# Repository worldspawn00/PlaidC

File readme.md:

# Plaid type C

Redesign of the Plaid PCB to use USBC and 2u stabilized layouts

Assembly and BOM generally follows the standard Plaid with the exception of the USBC port (USB4085-GF-A GCT) and 2 additional 5.1k resistors for C to C identification.  The PCB can also now take PCB-mount 2u stabilizers for the 2u spacebar locations, clip in or screw in will work.

https://github.com/hsgw/plaid/blob/master/doc/en/soldering.md

* Keyboard Maintainer: [Worldspawn00](https://github.com/Worldspawn00)

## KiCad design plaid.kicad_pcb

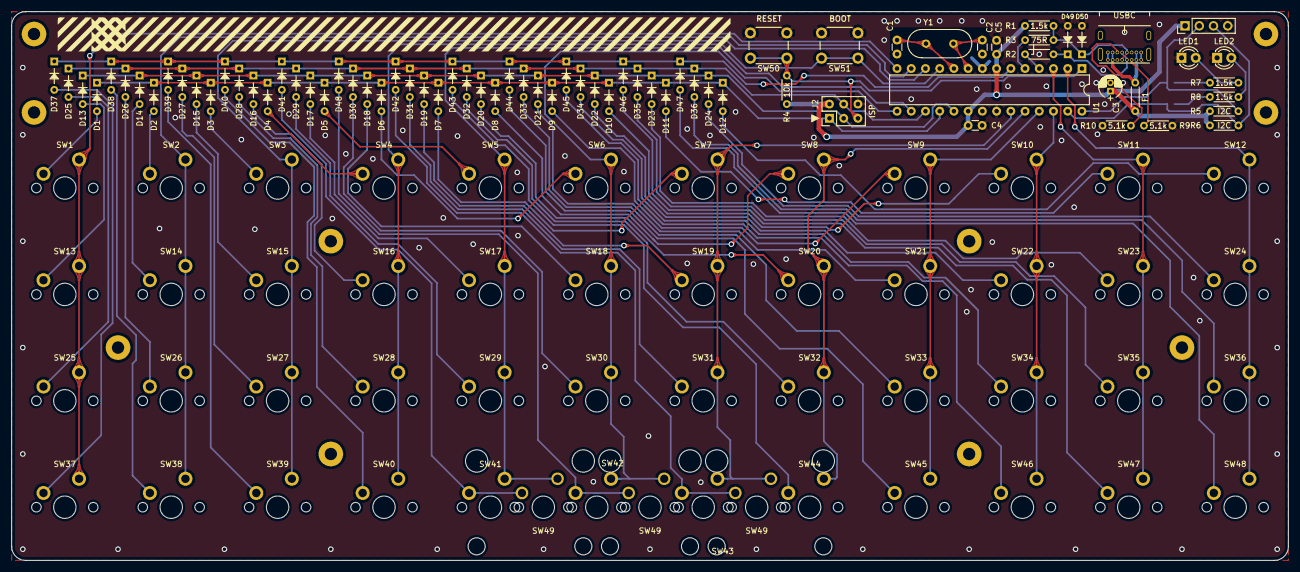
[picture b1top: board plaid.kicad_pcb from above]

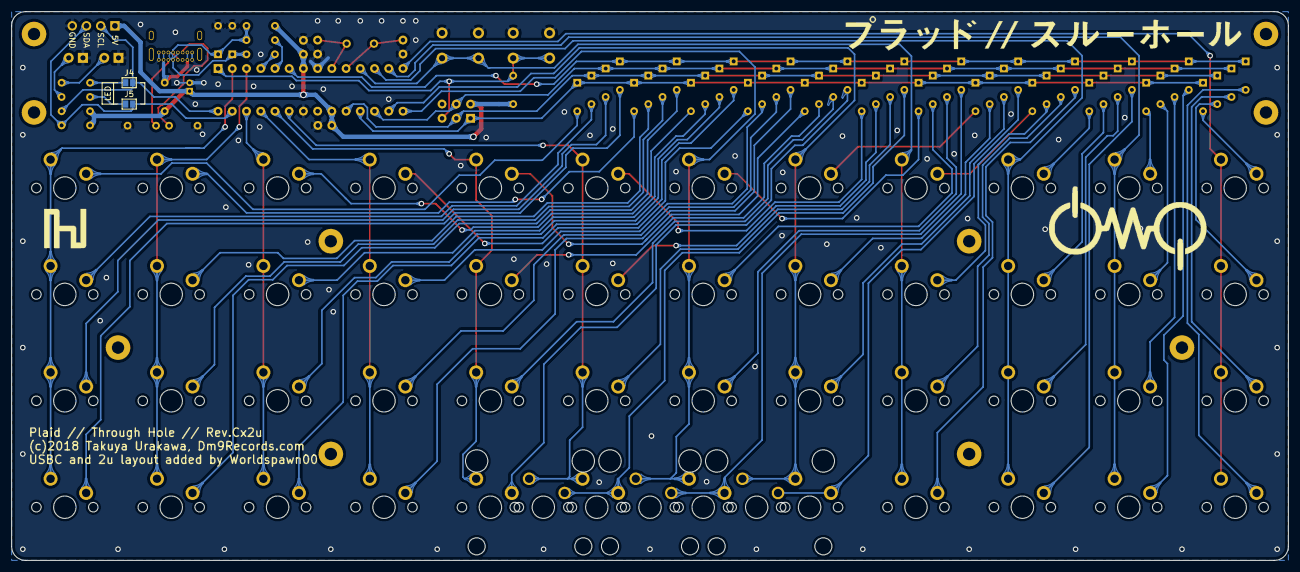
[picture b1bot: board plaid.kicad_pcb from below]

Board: 2 copper layers, 228.0 x 98.0 mm, 138 parts (2 on the bottom side), 80 nets.

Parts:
C1, C2: 20p; C_Disc_D3.0mm_W1.6mm_P2.50mm
C3: 4.7u; CP_Radial_D4.0mm_P1.50mm
C4, C5: 100n; C_Disc_D3.0mm_W1.6mm_P2.50mm
D1, D2, D3, D4, D5, D6, D7, D8, D9, D10, D11, D12, D13, D14, D15, D16, D17, D18, D19, D20, D21, D22, D23, D24, D25, D26, D27, D28, D29, D30, D31, D32, D33, D34, D35, D36, D37, D38, D39, D40, D41, D42, D43, D44, D45, D46, D47, D48: 1N4148; D_DO-35_SOD27_P5.08mm_Horizontal
D49, D50: 3.6V; D_DO-35_SOD27_P5.08mm_Horizontal
F1: 250mA; polyfuse_5.1mm
H1, H2, H3, H4, H5, H6, H7, H8, H9, H10: M2; MountingHole_2.2mm_M2_Pad
J2: AVR_ISP_6; Pin_Header_Straight_2x03_Pitch2.54mm
J3: Conn_01x04; Pin_Header_Straight_1x04_Pitch2.54mm
J4, J5: GS2
LED1: RED; LED_D3.0mm
LED2: GREEN; LED_D3.0mm
R1, R7, R8: 1.5k; R_Axial_DIN0204_L3.6mm_D1.6mm_P5.08mm_Horizontal
R2: 68R; R_Axial_DIN0204_L3.6mm_D1.6mm_P5.08mm_Horizontal
R3: 75R; R_Axial_DIN0204_L3.6mm_D1.6mm_P5.08mm_Horizontal
R4: 10k; R_Axial_DIN0204_L3.6mm_D1.6mm_P5.08mm_Horizontal
R5, R6: I2C; R_Axial_DIN0204_L3.6mm_D1.6mm_P5.08mm_Horizontal
R9, R10: 5.1k; R_Axial_DIN0204_L3.6mm_D1.6mm_P5.08mm_Horizontal
SW1, SW2, SW3, SW4, SW5, SW6, SW7, SW8, SW9, SW10, SW11, SW12, SW13, SW14, SW15, SW16, SW17, SW18, SW19, SW20, SW21, SW22, SW23, SW24, SW25, SW26, SW27, SW28, SW29, SW30, SW31, SW32, SW33, SW34, SW35, SW36, SW37, SW38, SW39, SW40, SW41, SW42, SW43, SW44, SW45, SW46, SW47, SW48: SW_Push; SW_Cherry_MX1A_1.00u_PCB
SW49, SW49#2, SW49#3: SW_Push; MXOnly-2U-ReversedStabilizers-NoLED
SW50: RESET; SW_PUSH_6mm
SW51: BOOT; SW_PUSH_6mm
U1: ATMEGA328-PU; DIP-28_W7.62mm
USBC: USB_C_USB4085; USB_C_GCT_USB4085
Y1: 16MHz; Crystal_HC49-4H_Vertical

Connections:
+5V: C3.1, C4.1, C5.1, F1.2, J2.2, J3.1, R1.2, R4.1, R5.1, R6.1, U1.7, U1.20
/COL0: SW1.2, SW13.2, SW25.2, SW37.2, U1.14
/COL1: SW2.2, SW14.2, SW26.2, SW38.2, U1.13
/COL2: SW3.2, SW15.2, SW27.2, SW39.2, U1.12
/COL3: SW4.2, SW16.2, SW28.2, SW40.2, SW51.1, U1.11
/COL4: SW5.2, SW17.2, SW29.2, SW41.2, SW49#2.2, U1.16
/COL5: SW6.2, SW18.2, SW30.2, SW42.2, SW49#3.2, U1.15
/COL6: SW7.2, SW19.2, SW31.2, SW43.2, SW49.2, U1.23
/COL7: SW8.2, SW20.2, SW32.2, SW44.2, U1.24
/COL8: SW9.2, SW21.2, SW33.2, SW45.2, U1.25
/COL9: SW10.2, SW22.2, SW34.2, SW46.2, U1.26
/COL10: SW11.2, SW23.2, SW35.2, SW47.2, U1.3
/COL11: SW12.2, SW24.2, SW36.2, SW48.2, U1.2
/RESET: J2.5, R4.2, SW50.1, U1.1
/ROW0: D1.1, D2.1, D3.1, D4.1, D5.1, D6.1, D7.1, D8.1, D9.1, D10.1, D11.1, D12.1, J2.1, U1.18
/ROW1: D13.1, D14.1, D15.1, D16.1, D17.1, D18.1, D19.1, D20.1, D21.1, D22.1, D23.1, D24.1, J2.3, U1.19
/ROW2: D25.1, D26.1, D27.1, D28.1, D29.1, D30.1, D31.1, D32.1, D33.1, D34.1, D35.1, D36.1, J2.4, U1.17
/ROW3: D37.1, D38.1, D39.1, D40.1, D41.1, D42.1, D43.1, D44.1, D45.1, D46.1, D47.1, D48.1, U1.6
/USB_D+: R2.1, U1.4
/USB_D-: R3.1, U1.5
/i2c_SCL: J3.2, J4.2, R5.2, U1.28
/i2c_SDA: J3.3, J5.2, R6.2, U1.27
GND: C1.2, C2.2, C3.2, C4.2, C5.2, D49.2, D50.2, J2.6, J3.4, LED1.1, LED2.1, R9.1, R10.1, SW50.2, SW51.2, U1.8, U1.22, USBC.A1, USBC.A12, USBC.B1, USBC.B12
unnamed: C1.1, U1.10, Y1.2
unnamed: C2.1, U1.9, Y1.1
unnamed: D1.2, SW1.1
unnamed: D2.2, SW2.1
unnamed: D3.2, SW3.1
unnamed: D4.2, SW4.1
unnamed: D5.2, SW5.1
unnamed: D6.2, SW6.1
unnamed: D7.2, SW7.1
unnamed: D8.2, SW8.1
unnamed: D9.2, SW9.1
unnamed: D10.2, SW10.1
unnamed: D11.2, SW11.1
unnamed: D12.2, SW12.1
unnamed: D13.2, SW13.1
unnamed: D14.2, SW14.1
unnamed: D15.2, SW15.1
unnamed: D16.2, SW16.1
unnamed: D17.2, SW17.1
unnamed: D18.2, SW18.1
unnamed: D19.2, SW19.1
unnamed: D20.2, SW20.1
unnamed: D21.2, SW21.1
unnamed: D22.2, SW22.1
unnamed: D23.2, SW23.1
unnamed: D24.2, SW24.1
unnamed: D25.2, SW25.1
unnamed: D26.2, SW26.1
unnamed: D27.2, SW27.1
unnamed: D28.2, SW28.1
unnamed: D29.2, SW29.1
unnamed: D30.2, SW30.1
unnamed: D31.2, SW31.1
unnamed: D32.2, SW32.1
unnamed: D33.2, SW33.1
unnamed: D34.2, SW34.1
unnamed: D35.2, SW35.1
unnamed: D36.2, SW36.1
unnamed: D37.2, SW37.1
unnamed: D38.2, SW38.1
unnamed: D39.2, SW39.1
unnamed: D40.2, SW40.1
unnamed: D41.2, SW41.1, SW49#2.1
unnamed: D42.2, SW43.1, SW49.1
unnamed: D43.2, SW44.1
unnamed: D44.2, SW45.1
unnamed: D45.2, SW46.1
unnamed: D46.2, SW47.1
unnamed: D47.2, SW48.1
unnamed: D48.2, SW42.1, SW49#3.1
unnamed: D49.1, R2.2, USBC.A6, USBC.B6
unnamed: D50.1, R1.1, R3.2, USBC.A7, USBC.B7
unnamed: F1.1, USBC.A4, USBC.A9, USBC.B4, USBC.B9
unnamed: J4.1, R7.1
unnamed: J5.1, R8.1
unnamed: LED1.2, R7.2
unnamed: LED2.2, R8.2

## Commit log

2020-05-28 generating gerbers
2020-06-13 fixing spacebar footprints
2020-06-14 adding 2x2u layout
2020-06-14 fix resistor value

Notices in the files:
plaid.kicad_pcb:
(c)2018 Takuya Urakawa, Dm9Records.com
